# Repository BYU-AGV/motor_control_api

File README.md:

#motor_control_api
 API for motor control, AGV 2020

./xbox_processing_str contains the Processing (Java Library) code. This interfaces with the USB Logitech xbox controller. Run ./xbox_processing_str/xbox_processing_str.pde with Processing, which can be downloaded from [link](https://processing.org/download/). Make sure to update the COM port to whatever the Arduino is on

./motor_control_platformio contains the Arduino motor control code. It can be compiled and uploaded easily using PlatformIO.

./motor_control_API contains higher level motorController class and .h file

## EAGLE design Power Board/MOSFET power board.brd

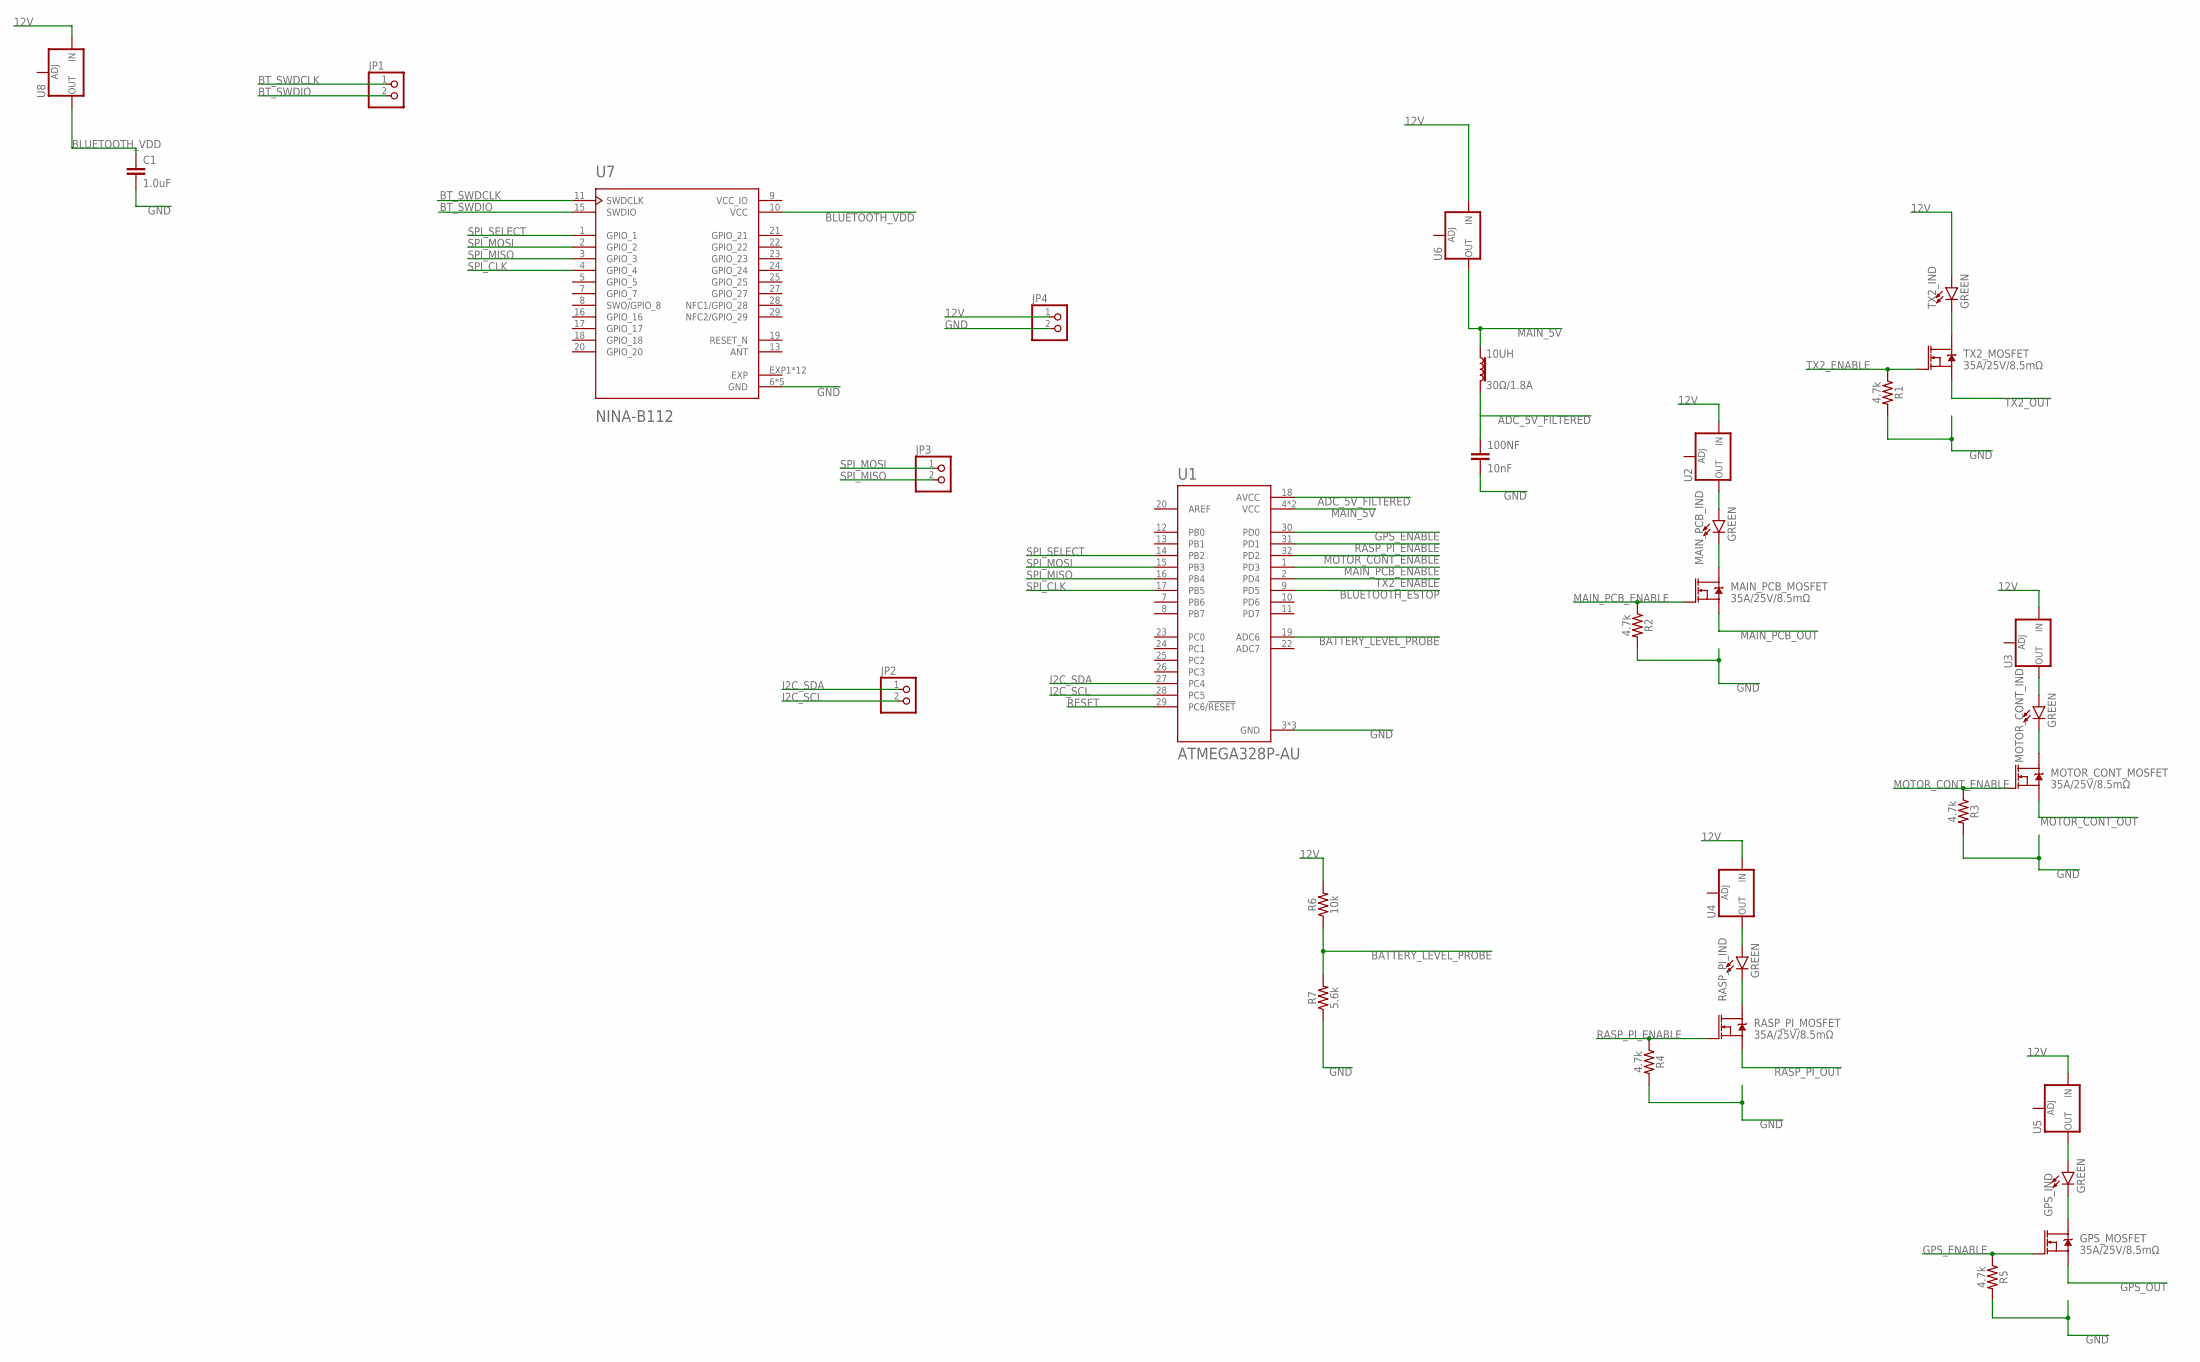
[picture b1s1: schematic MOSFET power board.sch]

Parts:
10UH: 30Ω/1.8A; 0603
100NF: 10nF; 0603
C1: 1.0uF; 0603
GPS_IND: GREEN; LED-0603
GPS_MOSFET: 35A/25V/8.5mΩ; DPAK
JP1, JP2, JP3, JP4: PINHD-1X2; 1X02
MAIN_PCB_IND: GREEN; LED-0603
MAIN_PCB_MOSFET: 35A/25V/8.5mΩ; DPAK
MOTOR_CONT_IND: GREEN; LED-0603
MOTOR_CONT_MOSFET: 35A/25V/8.5mΩ; DPAK
R1, R2, R3, R4, R5: 4.7k; 0603
R6: 10k; 0603
R7: 5.6k; 0603
RASP_PI_IND: GREEN; LED-0603
RASP_PI_MOSFET: 35A/25V/8.5mΩ; DPAK
TX2_IND: GREEN; LED-0603
TX2_MOSFET: 35A/25V/8.5mΩ; DPAK
U1: ATMEGA328P-AU; QFP80P900X900X120-32N
U2, U3, U4, U5, U6, U8: V_REG_LM1117SOT223; SOT223
U7: NINA-B112; UBLOX_NINA-B112

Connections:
12V: JP4.1, R6.2, TX2_IND.A, U2.3 (IN), U3.3 (IN), U4.3 (IN), U5.3 (IN), U6.3 (IN), U8.3 (IN)
ADC_5V_FILTERED: 10UH.2, 100NF.1, U1.18 (AVCC)
BATTERY_LEVEL_PROBE: R6.1, R7.2, U1.19 (ADC6)
BLUETOOTH_ESTOP: U1.9 (PD5)
BLUETOOTH_VDD: C1.1, U7.10 (VCC), U8.2 (OUT), U8.4 (OUT)
BT_SWDCLK: JP1.1, U7.11 (SWDCLK)
BT_SWDIO: JP1.2, U7.15 (SWDIO)
EXP: U7.EXP1 (EXP), U7.EXP2 (EXP), U7.EXP3 (EXP), U7.EXP4 (EXP), U7.EXP5 (EXP), U7.EXP6 (EXP), U7.EXP7 (EXP), U7.EXP8 (EXP), U7.EXP9 (EXP), U7.EXP10 (EXP), U7.EXP11 (EXP), U7.EXP12 (EXP)
GND: 100NF.2, C1.2, JP4.2, R1.2, R2.2, R3.2, R4.2, R5.2, R7.1, U1.3 (GND), U1.5 (GND), U1.21 (GND), U7.6 (GND), U7.12 (GND), U7.14 (GND), U7.26 (GND), U7.30 (GND)
GPS_ENABLE: GPS_MOSFET.1 (G), R5.1, U1.30 (PD0)
GPS_OUT: GPS_MOSFET.3 (S)
I2C_SCL: JP2.2, U1.28 (PC5)
I2C_SDA: JP2.1, U1.27 (PC4)
MAIN_5V: 10UH.1, U1.4 (VCC), U1.6 (VCC), U6.2 (OUT), U6.4 (OUT)
MAIN_PCB_ENABLE: MAIN_PCB_MOSFET.1 (G), R2.1, U1.1 (PD3)
MAIN_PCB_OUT: MAIN_PCB_MOSFET.3 (S)
MOTOR_CONT_ENABLE: MOTOR_CONT_MOSFET.1 (G), R3.1, U1.32 (PD2)
MOTOR_CONT_OUT: MOTOR_CONT_MOSFET.3 (S)
unnamed: MAIN_PCB_IND.C, MAIN_PCB_MOSFET.4 (D)
unnamed: MAIN_PCB_IND.A, U2.2 (OUT), U2.4 (OUT)
unnamed: MOTOR_CONT_IND.C, MOTOR_CONT_MOSFET.4 (D)
unnamed: MOTOR_CONT_IND.A, U3.2 (OUT), U3.4 (OUT)
unnamed: RASP_PI_IND.C, RASP_PI_MOSFET.4 (D)
unnamed: RASP_PI_IND.A, U4.2 (OUT), U4.4 (OUT)
unnamed: GPS_IND.C, GPS_MOSFET.4 (D)
unnamed: GPS_IND.A, U5.2 (OUT), U5.4 (OUT)
unnamed: TX2_IND.C, TX2_MOSFET.4 (D)
RASP_PI_ENABLE: R4.1, RASP_PI_MOSFET.1 (G), U1.31 (PD1)
RASP_PI_OUT: RASP_PI_MOSFET.3 (S)
RESET: U1.29 (PC6/!RESET)
SPI_CLK: U1.17 (PB5), U7.4 (GPIO_4)
SPI_MISO: JP3.2, U1.16 (PB4), U7.3 (GPIO_3)
SPI_MOSI: JP3.1, U1.15 (PB3), U7.2 (GPIO_2)
SPI_SELECT: U1.14 (PB2), U7.1 (GPIO_1)
TX2_ENABLE: R1.1, TX2_MOSFET.1 (G), U1.2 (PD4)
TX2_OUT: TX2_MOSFET.3 (S)
VCC_IO: U7.9 (VCC_IO)

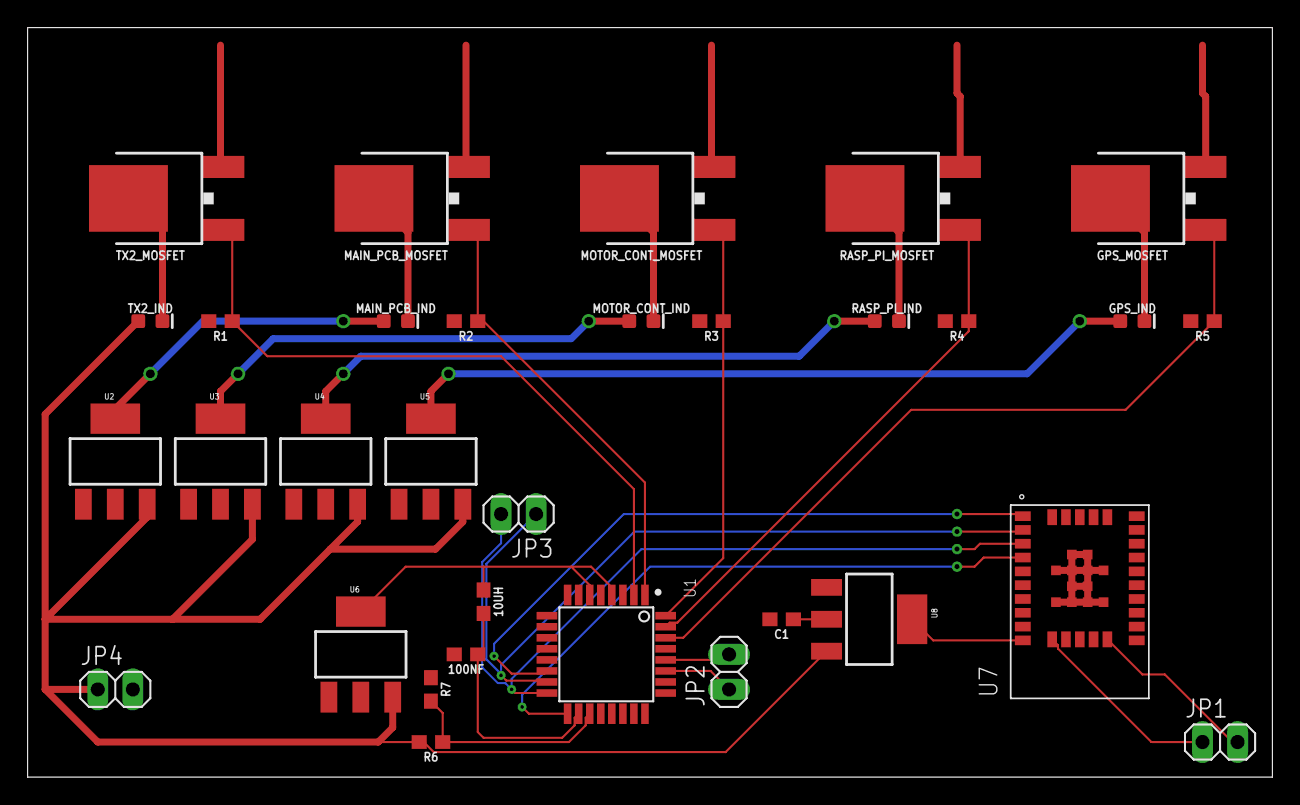
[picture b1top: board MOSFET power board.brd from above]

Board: 2 copper layers, 90.2 x 54.3 mm, 32 parts (0 on the bottom side), 29 nets.

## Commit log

2019-11-04 stepped control initial commit
    updated for stepped control
2019-11-04 active update initial commit
2019-11-16 switched to platformio
2019-11-16 added two_joystick
2019-11-16 Update xbox_processing.pde
    Works for two joysticks
2019-11-16 Update xbox_processing.pde
    printing update
2019-11-19 Changes to be committed: modified: motor_control_platformio/src/main.cpp modified: motor_control_platformio/src/motor.cpp modified: motor_control_platformio/src/motor.h modified: motor_control_platfo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
2019-11-20 updates - fully functional now
2019-11-21 added comments
2019-12-05 Updated files
    Changed file names, defined state machine states
2019-12-05 Fixed initialization list syntax
2019-12-05 updated motor controller
    Added forward, backward direction for motion controls
    Inlined small functions
    Fleshed out state machine a bit
2019-12-05 syntax change
2019-12-06 Several changes
    Changed from single target speed and direction to targets for each wheel
    Created simple design for straight line and radius turn
2019-12-07 basic implementation
2019-12-07 Skeletonized control functions
2019-12-23 I2C commands for main brain
2019-12-23 Added raspberry pi testing file
2019-12-24 ade classes for motor test and encoder simulator
2020-01-13 added i2c command syntax, command parsing
2020-01-13 Spelling fixes
2020-01-13 syntax fixing
2020-01-13 grammar fixes
2020-01-18 Matlab code for PI controller
    PI control for motors
2020-01-18 Fixed i2c structures
2020-01-18 Added Arduino files
2020-01-25 organized file structure
2020-01-25 init
2020-01-28 initial PID C code upload
2020-01-28 removed swp files
2020-01-28 added i2c example
2020-01-28 Changed Arduino setup for new H-bridge
2020-01-28 Implemented Sabertooth
2020-02-01 updated for new h-bridge
2020-02-01 created interactive example
2020-02-01 got working with h-bridge and i2c
2020-02-08 added interface class for simple i2c control
2020-02-08 i2c is working
2020-02-08 worked on active update
2020-02-08 asctive update works over i2c
2020-02-15 updated xbox controller to work with sabertooth
2020-02-22 changed names
2020-02-22 finish renaming
2020-02-22 dummy encoder class
2020-02-22 created PID class/function
2020-02-22 modified motor control class for pid/encoders
2020-02-29 added class for the encoder. see main for template on how to use
2020-02-29 made xbox control for control
2020-02-29 removed unnecessary code (comments)
2020-02-29 updated encoder function
2020-02-29 set up input to target function
2020-02-29 added info on how to implement in main
2020-02-29 updated logic
2020-02-29 added encoder files
2020-02-29 interrupt wrappers in pid
2020-02-29 encoder updates
2020-02-29 i2c recieve from TX2
2020-04-01 Added power board schematic

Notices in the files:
parts and their libraries:
SparkFun-LED: Licensing: Creative Commons ShareAlike 4.0 International - https://creativecommons.org/licenses/by-sa/4.0
